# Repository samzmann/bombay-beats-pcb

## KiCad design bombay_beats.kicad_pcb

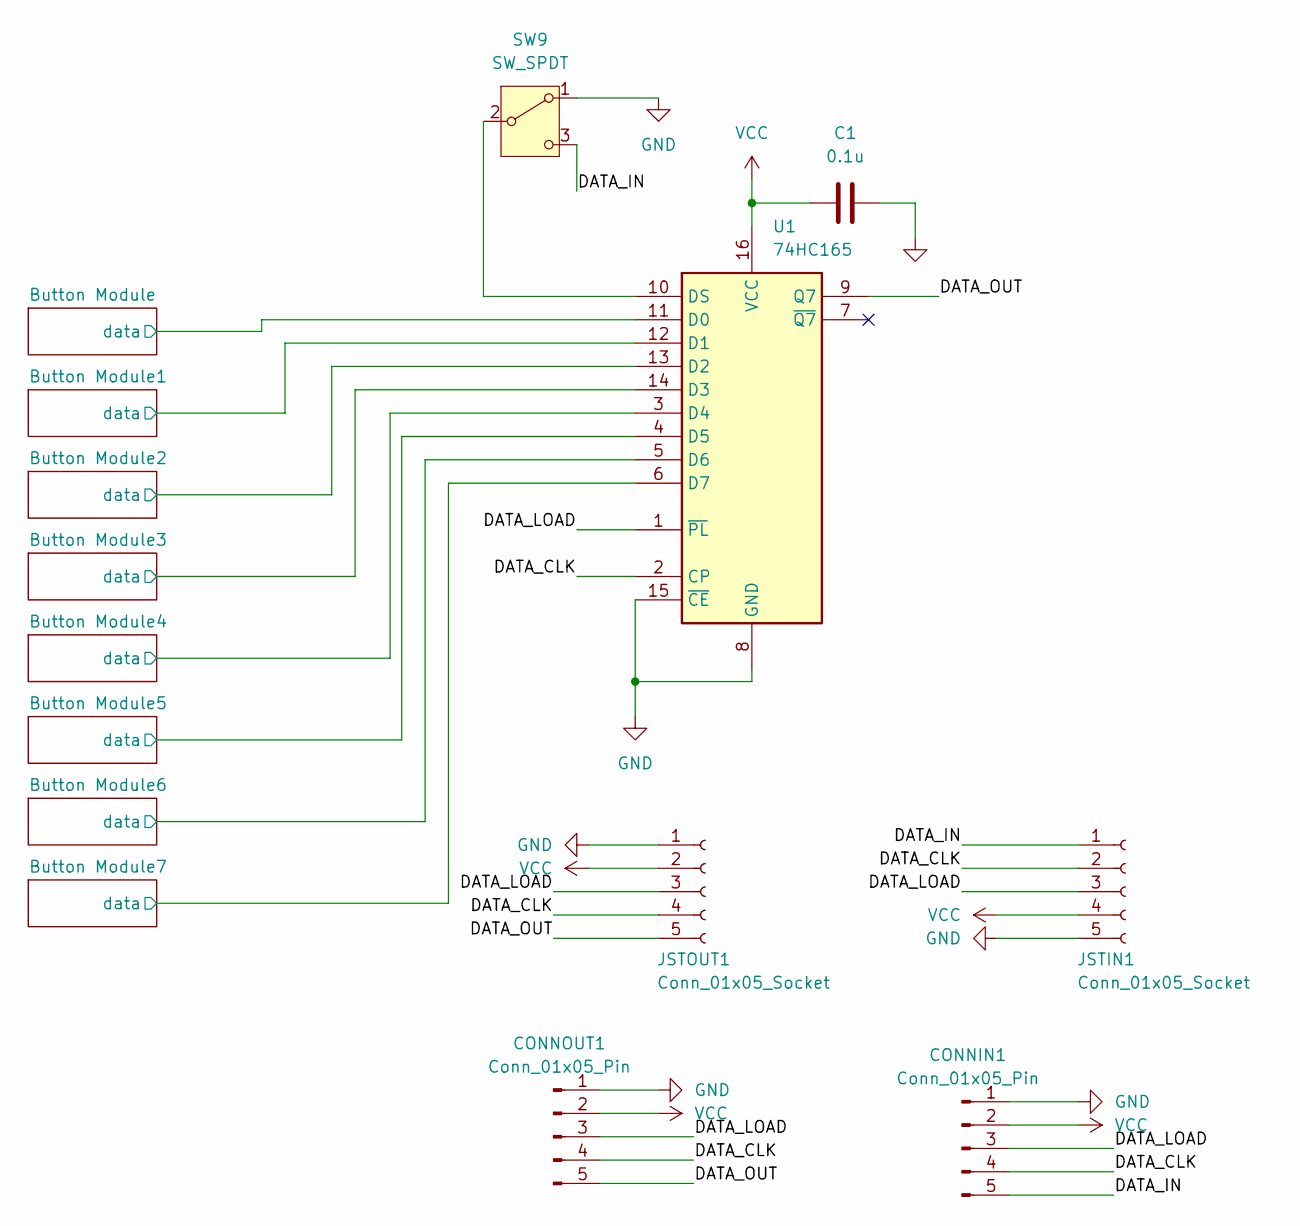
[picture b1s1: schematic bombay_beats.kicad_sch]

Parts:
C1: 0.1u; C_0603_1608Metric; LCSC Part # C1322361
CONNIN1: Conn_01x05_Pin; PinHeader_1x05_P2.54mm_Vertical
CONNOUT1: Conn_01x05_Pin; PinHeader_1x05_P2.54mm_Vertical
JSTIN1: Conn_01x05_Socket; JST_SH_SM05B-SRSS-TB_1x05-1MP_P1.00mm_Horizontal; LCSC Part # C136657
JSTOUT1: Conn_01x05_Socket; JST_SH_SM05B-SRSS-TB_1x05-1MP_P1.00mm_Horizontal; LCSC Part # C136657
SW9: SW_SPDT; SW_SPDT_PCM12
U1: 74HC165; TSSOP-16-1EP_4.4x5mm_P0.65mm_EP3x3mm_ThermalVias; LCSC Part # C80093

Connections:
/Button Module1/data: U1.12 (D1); also elsewhere on the board
/Button Module2/data: U1.13 (D2); also elsewhere on the board
/Button Module3/data: U1.14 (D3); also elsewhere on the board
/Button Module4/data: U1.3 (D4); also elsewhere on the board
/Button Module5/data: U1.4 (D5); also elsewhere on the board
/Button Module6/data: U1.5 (D6); also elsewhere on the board
/Button Module7/data: U1.6 (D7); also elsewhere on the board
/Button Module/data: U1.11 (D0); also elsewhere on the board
/DATA_CLK: CONNIN1.4, CONNOUT1.4, JSTIN1.2, JSTOUT1.4, U1.2 (CP)
/DATA_IN: CONNIN1.5, JSTIN1.1, SW9.3 (C)
/DATA_LOAD: CONNIN1.3, CONNOUT1.3, JSTIN1.3, JSTOUT1.3, U1.1 (~PL)
/DATA_OUT: CONNOUT1.5, JSTOUT1.5, U1.9 (Q7)
GND: C1.2, CONNIN1.1, CONNOUT1.1, JSTIN1.5, JSTOUT1.1, SW9.1 (A), U1.8 (GND), U1.15 (~CE); also elsewhere on the board
unnamed: SW9.2 (B), U1.10 (DS)
VCC: C1.1, CONNIN1.2, CONNOUT1.2, JSTIN1.4, JSTOUT1.2, U1.16 (VCC); also elsewhere on the board

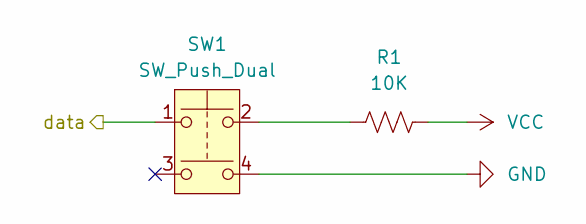
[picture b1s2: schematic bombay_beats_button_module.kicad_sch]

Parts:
R1: 10K; R_0603_1608Metric; LCSC Part # C25804
SW1: SW_Push_Dual; 4.5 Push Button Switch JLCPCB; LCSC Part # C2844397

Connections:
/Button Module/data: SW1.1; also elsewhere on the board
GND: SW1.4; also elsewhere on the board
unnamed: R1.1, SW1.2
VCC: R1.2; also elsewhere on the board

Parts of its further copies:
R2, R3, R4, R5, R6, R7, R8: 10K; R_0603_1608Metric; LCSC Part # C25804
SW2, SW3, SW4, SW5, SW6, SW7, SW8: SW_Push_Dual; 4.5 Push Button Switch JLCPCB; LCSC Part # C2844397

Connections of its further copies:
/Button Module1/data: SW2.1; also elsewhere on the board
/Button Module2/data: SW3.1; also elsewhere on the board
/Button Module3/data: SW4.1; also elsewhere on the board
/Button Module4/data: SW5.1; also elsewhere on the board
/Button Module5/data: SW6.1; also elsewhere on the board
/Button Module6/data: SW7.1; also elsewhere on the board
/Button Module7/data: SW8.1; also elsewhere on the board
GND: SW2.4, SW3.4, SW4.4, SW5.4, SW6.4, SW7.4, SW8.4; also elsewhere on the board
unnamed: R2.1, SW2.2
unnamed: R3.1, SW3.2
unnamed: R4.1, SW4.2
unnamed: R5.1, SW5.2
unnamed: R6.1, SW6.2
unnamed: R7.1, SW7.2
unnamed: R8.1, SW8.2
VCC: R2.2, R3.2, R4.2, R5.2, R6.2, R7.2, R8.2; also elsewhere on the board

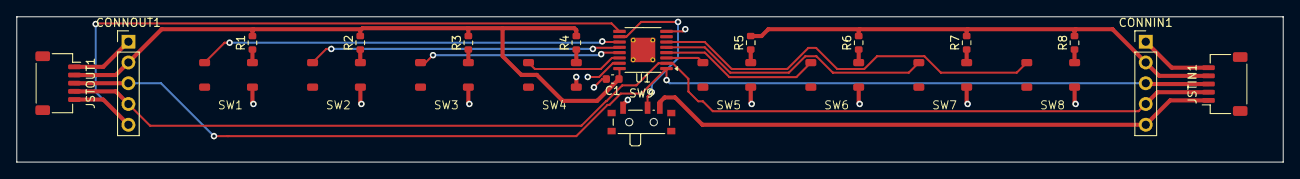
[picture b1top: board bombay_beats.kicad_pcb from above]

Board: 2 copper layers, 154.9 x 17.8 mm, 23 parts (0 on the bottom side), 23 nets.

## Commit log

2024-04-18 2 sided pcb version
2024-04-22 one sided version
2024-05-01 finalize one sided smd version
2024-05-01 replace footprints for through hole version
2024-05-08 production files
2024-05-08 fix 0603 footprints
2024-06-15 fix pinout of jst input
